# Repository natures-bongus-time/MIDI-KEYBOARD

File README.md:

# MIDI keyboard
## what it is
This midi keyboard is a midi controller with a pcb, swithces, a rotary encoder, and a bourns slide capacitator.
## WHY it was made: 
as a beginner project for half life weeks three and eight.
## pictures

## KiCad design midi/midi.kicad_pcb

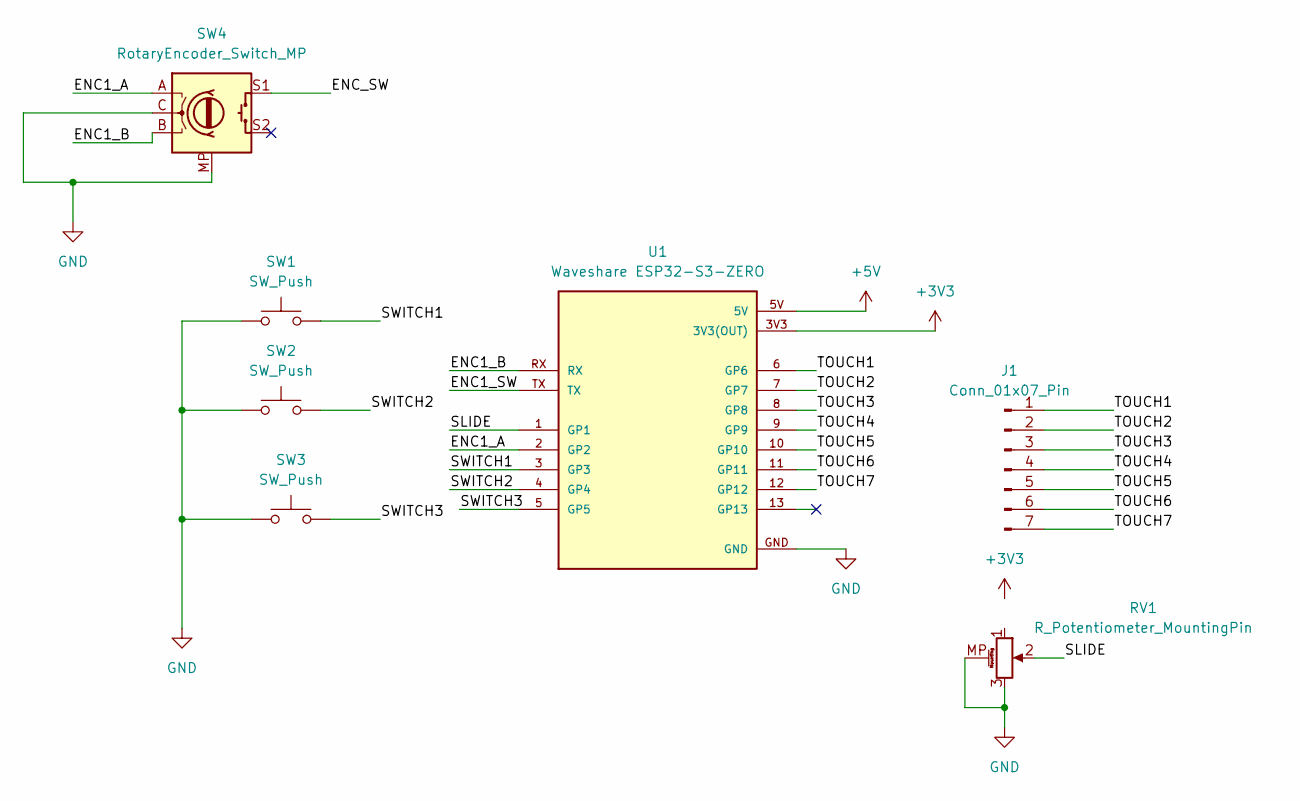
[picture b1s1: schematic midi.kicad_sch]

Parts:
J1: Conn_01x07_Pin; EXISTS
RV1: R_Potentiometer_MountingPin; Potentiometer_Bourns_PTA1543_Single_Slide
SW1, SW2, SW3: SW_Push; Kailh Choc Low-Profile Switches
SW4: RotaryEncoder_Switch_MP; RotaryEncoder_Alps_EC11E-Switch_Vertical_H20mm
U1: Waveshare ESP32-S3-ZERO; Waveshare ESP32-S3-Zero; PARTREV NA

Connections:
+3V3: U1.3V3 (3V3(OUT))
+5V: U1.5V
/ENC1_A: SW4.A, U1.2 (GP2)
/ENC1_B: SW4.B, U1.RX
/ENC1_SW: U1.TX
/ENC_SW: SW4.S1
/SLIDE: RV1.2, U1.1 (GP1)
/SWITCH1: SW1.2, U1.3 (GP3)
/SWITCH2: SW2.2, U1.4 (GP4)
/SWITCH3: SW3.2, U1.5 (GP5)
/TOUCH1: J1.1, U1.6 (GP6)
/TOUCH2: J1.2, U1.7 (GP7)
/TOUCH3: J1.3, U1.8 (GP8)
/TOUCH4: J1.4, U1.9 (GP9)
/TOUCH5: J1.5, U1.10 (GP10)
/TOUCH6: J1.6, U1.11 (GP11)
/TOUCH7: J1.7, U1.12 (GP12)
GND: RV1.3, RV1.MP (MountPin), SW1.1, SW2.1, SW3.1, SW4.C, SW4.MP, U1.GND

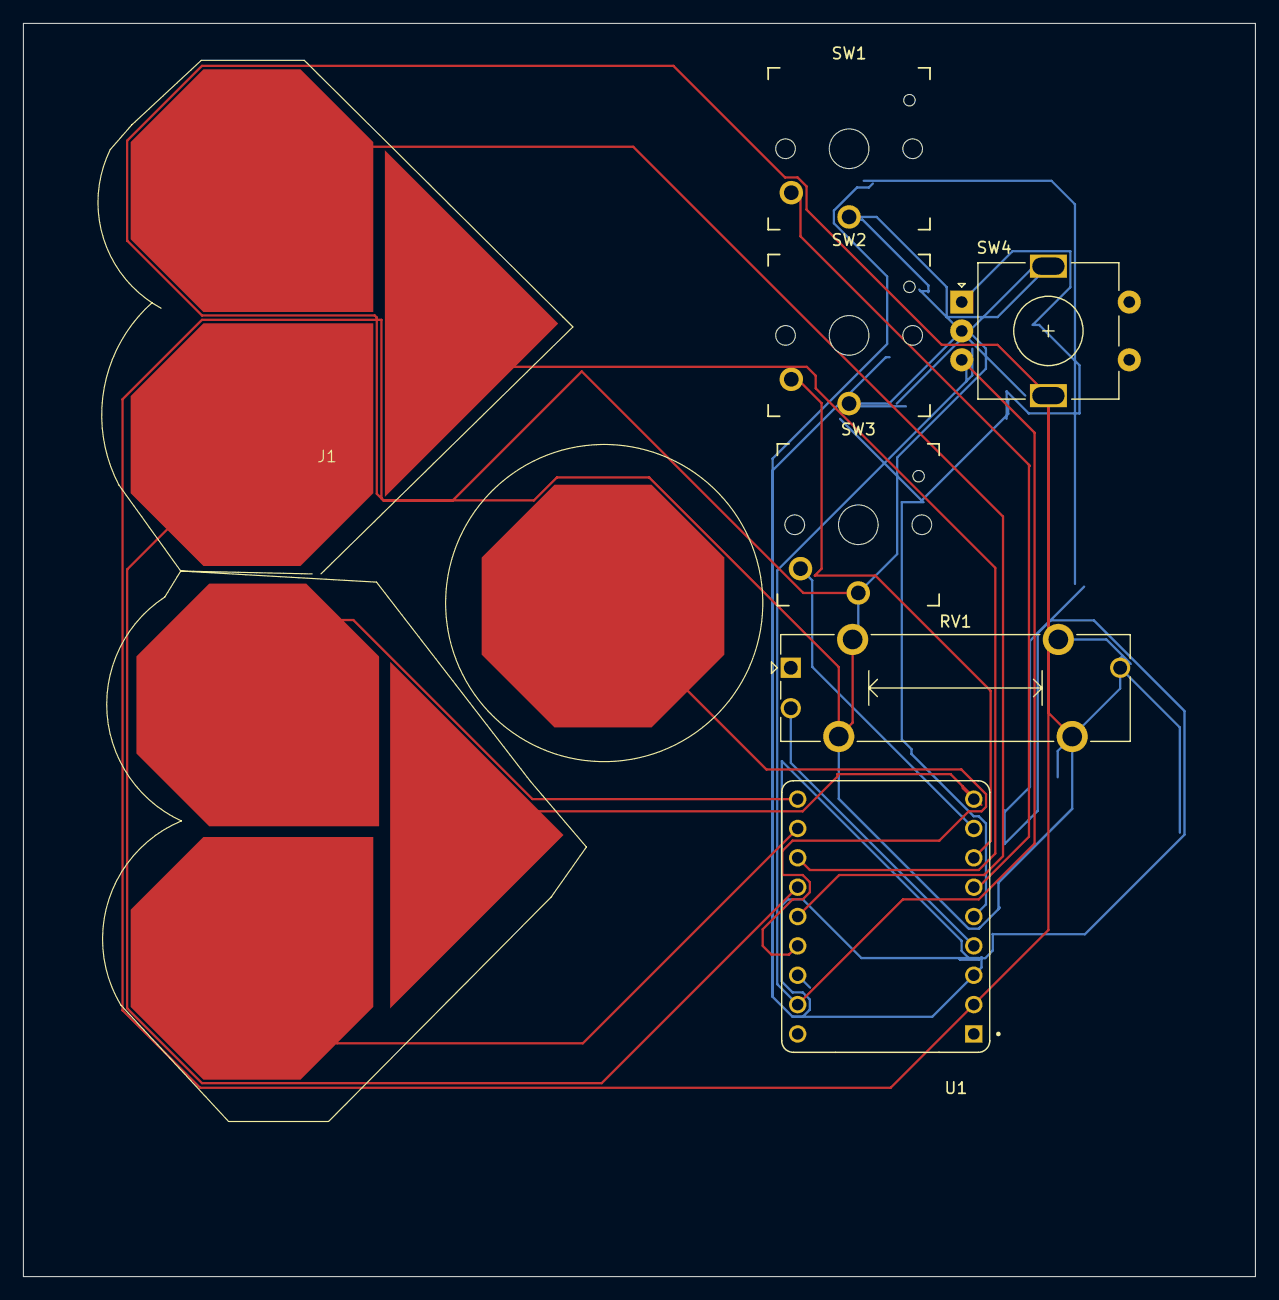
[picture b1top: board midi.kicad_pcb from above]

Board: 2 copper layers, 106.6 x 108.4 mm, 7 parts (0 on the bottom side), 14 nets.
